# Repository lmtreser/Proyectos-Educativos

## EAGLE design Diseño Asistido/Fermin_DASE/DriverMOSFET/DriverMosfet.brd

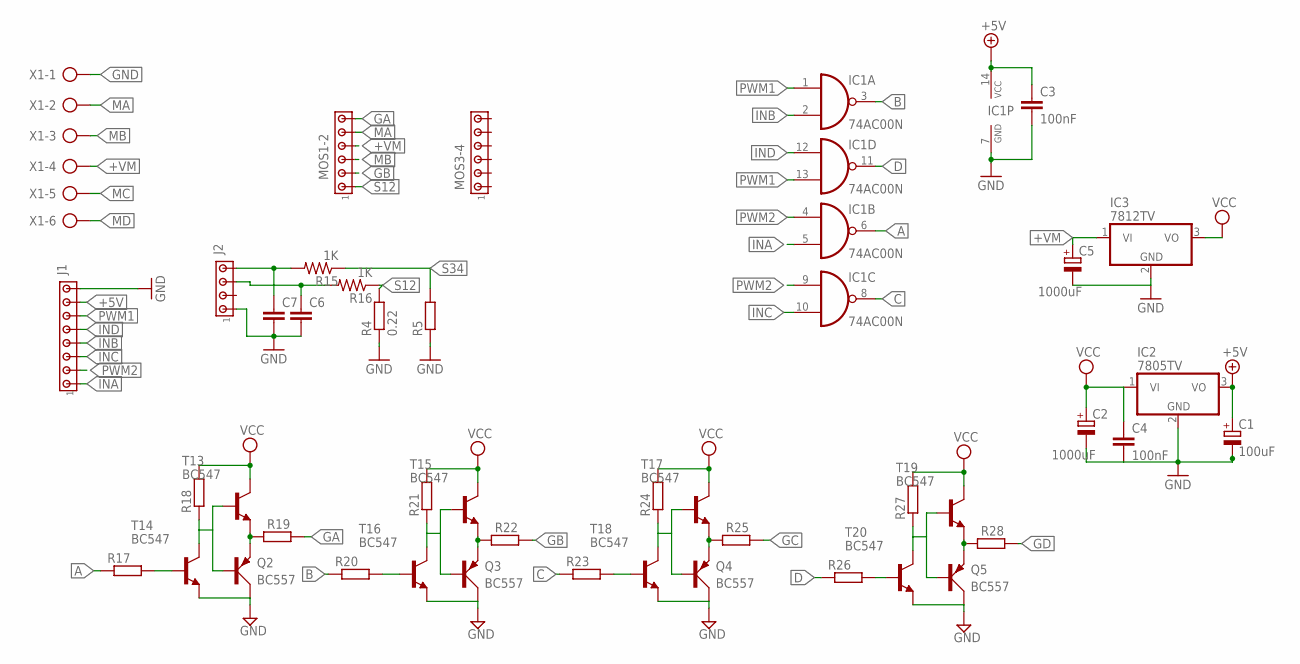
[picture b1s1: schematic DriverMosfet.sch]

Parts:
C1: 100uF; E2,5-6
C2: 1000uF; E3,5-8
C3, C4: 100nF; C050-025X075
C5: 1000uF; E3,5-10
C6, C7: C-EU025-025X050; C025-025X050
IC1: 74AC00N; DIL14
IC2: 7805TV; TO220V
IC3: 7812TV; TO220V
J1: MTA08-100; 10X08MTA
J2: MTA04-100; 10X04MTA
MOS1-2, MOS3-4: MTA06-100; 10X06MTA
Q2, Q3, Q4, Q5: BC557; SOT54A
R4: 0.22; 0411/12
R5: R-EU_0411/12; 0411/12
R15, R16: 1K; 0207/7@1
R17, R18, R19, R20, R21, R22, R23, R24, R25, R26, R27, R28: R-EU_0207/7; 0207/7
T13, T14, T15, T16, T17, T18, T19, T20: BC547; TO92
X1: AK500/6-H

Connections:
+5V: C1.+, C3.1, IC1.14 (VCC), IC2.3 (VO), J1.7
+VM: C5.+, IC3.1 (VI), MOS1-2.4, X1.4
A: IC1.6 (O), R17.1
B: IC1.3 (O), R20.1
C: IC1.8 (O), R23.1
D: IC1.11 (O), R26.1
GA: MOS1-2.6, R19.2
GB: MOS1-2.2, R22.2
GC: R25.2
GD: R28.2
GND: C1.-, C2.-, C3.2, C4.2, C5.-, C6.2, IC1.7 (GND), IC2.2 (GND), IC3.2 (GND), J1.8, J2.1, Q2.C, Q3.C, Q4.C, Q5.C, R4.1, R5.1, T14.1 (E), T16.1 (E), T18.1 (E), T20.1 (E), X1.1
INA: IC1.5 (I1), J1.1
INB: IC1.2 (I1), J1.4
INC: IC1.10 (I1), J1.3
IND: IC1.12 (I0), J1.5
MA: MOS1-2.5, X1.2
MB: MOS1-2.3, X1.3
MC: X1.5
MD: X1.6
unnamed: C7.1, J2.4, R15.2
unnamed: R17.2, T14.2 (B)
unnamed: C6.1, J2.3, R16.2
unnamed: Q3.E, R22.1, T15.1 (E)
unnamed: Q2.E, R19.1, T13.1 (E)
unnamed: Q4.E, R25.1, T17.1 (E)
unnamed: Q2.B, R18.1, T13.2 (B), T14.3 (C)
unnamed: R23.2, T18.2 (B)
unnamed: Q4.B, R24.1, T17.2 (B), T18.3 (C)
unnamed: R20.2, T16.2 (B)
unnamed: Q3.B, R21.1, T15.2 (B), T16.3 (C)
unnamed: Q5.E, R28.1, T19.1 (E)
unnamed: R26.2, T20.2 (B)
unnamed: Q5.B, R27.1, T19.2 (B), T20.3 (C)
PWM1: IC1.1 (I0), IC1.13 (I1), J1.6
PWM2: IC1.4 (I0), IC1.9 (I0), J1.2
S12: MOS1-2.1, R4.2, R16.1
S34: R5.2, R15.1
VCC: C2.+, C4.1, IC2.1 (VI), IC3.3 (VO), R18.2, R21.2, R24.2, R27.2, T13.3 (C), T15.3 (C), T17.3 (C), T19.3 (C)

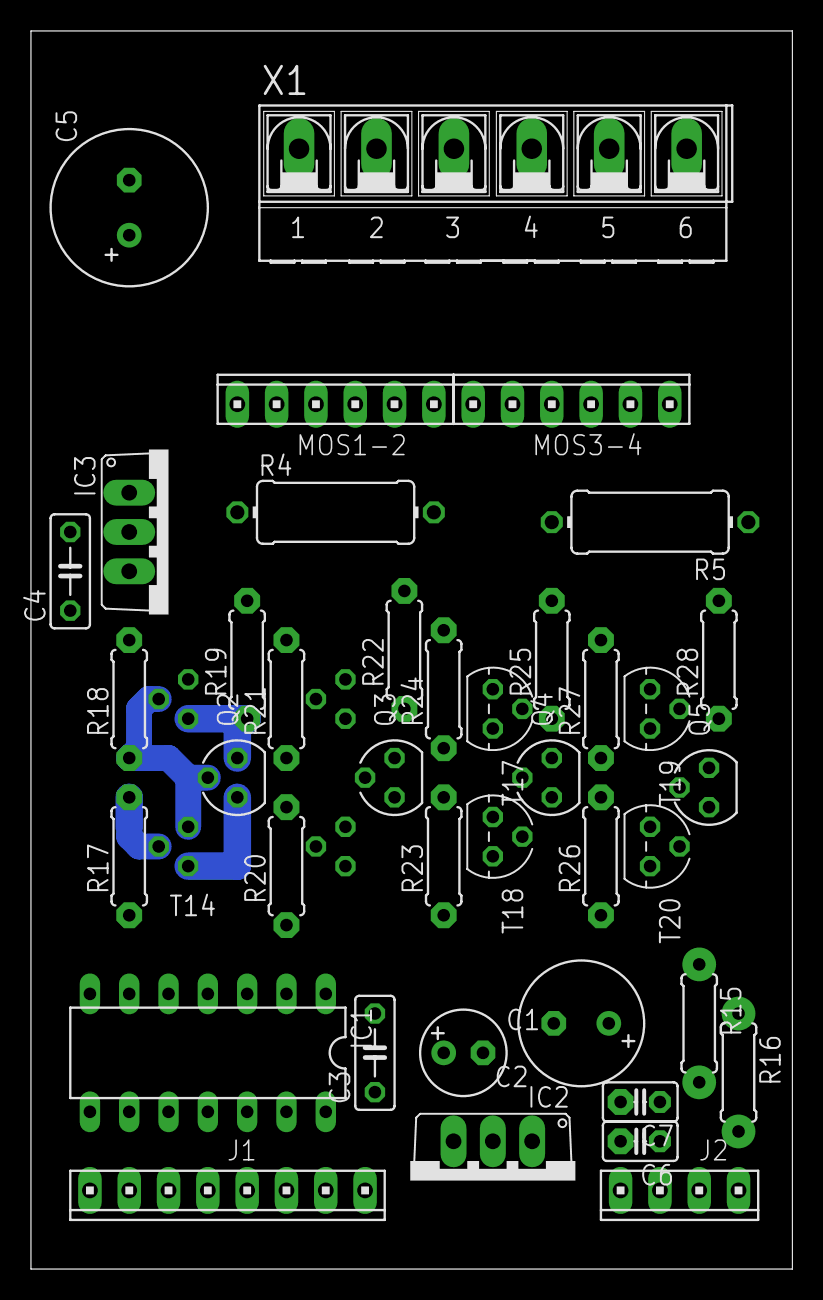
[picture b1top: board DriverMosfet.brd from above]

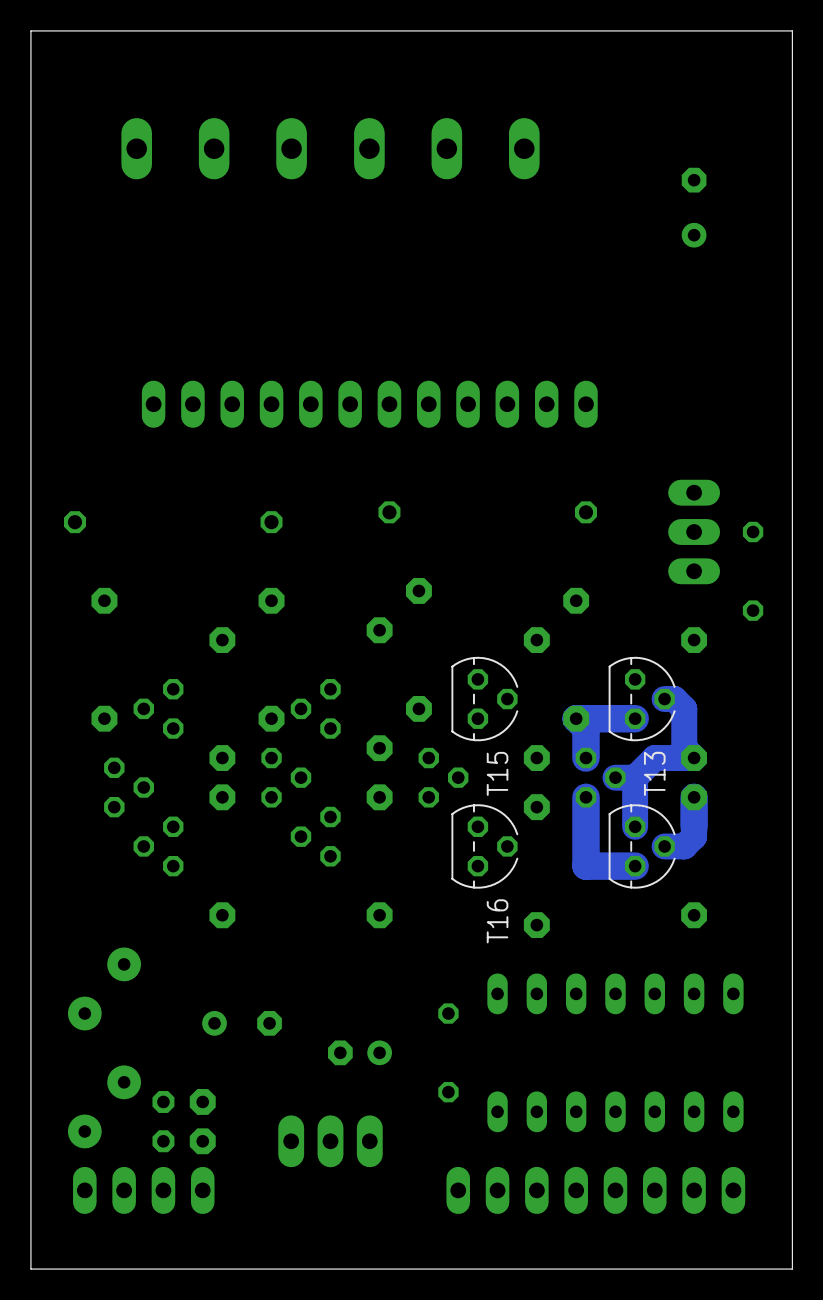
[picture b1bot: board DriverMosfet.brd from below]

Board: 2 copper layers, 49.2 x 80.0 mm, 43 parts (4 on the bottom side), 34 nets.

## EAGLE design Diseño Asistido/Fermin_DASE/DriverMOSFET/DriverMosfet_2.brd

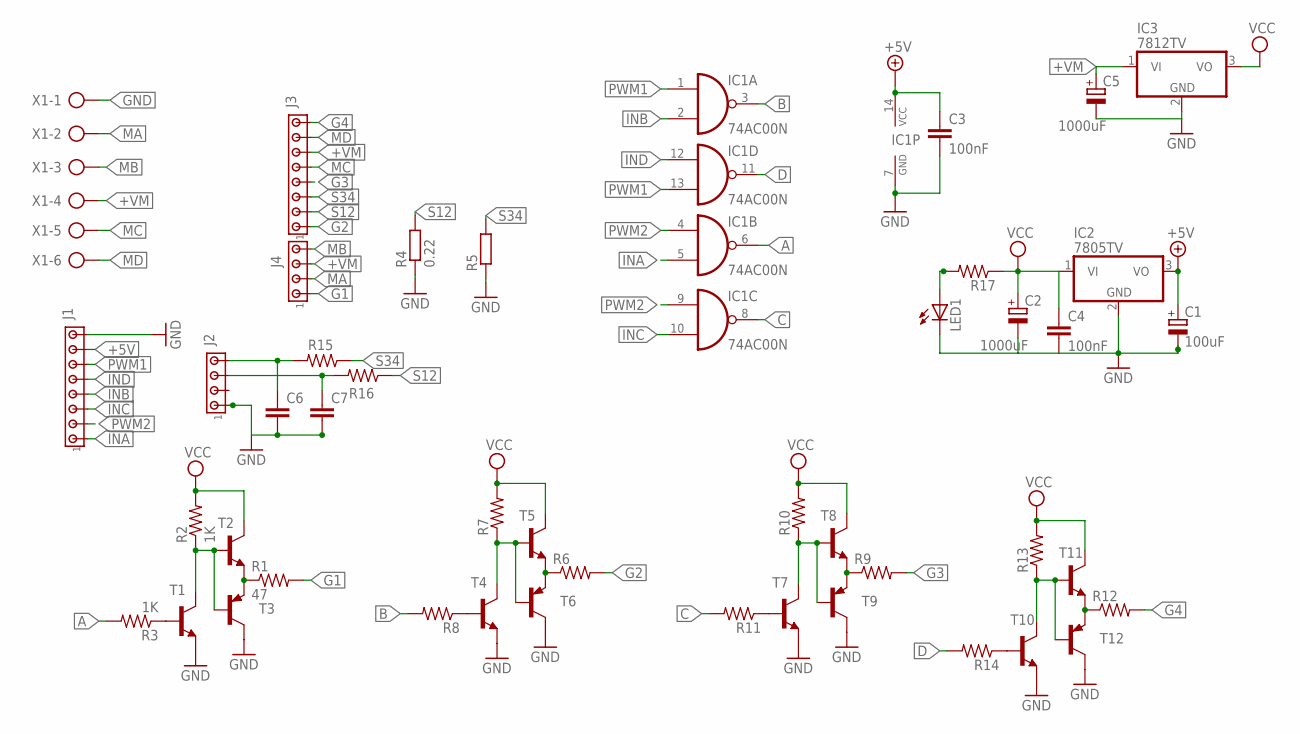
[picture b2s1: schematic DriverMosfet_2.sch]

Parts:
C1: 100uF; E2,5-6
C2: 1000uF; E2,5-7
C3, C4: 100nF; C050-025X075
C5: 1000uF; E3,5-10
C6, C7: C-EU025-030X050; C025-030X050
IC1: 74AC00N; DIL14
IC2: 7805TV; TO220V
IC3: 7812TV; TO220V
J1, J3: MTA08-100; 10X08MTA
J2, J4: MTA04-100; 10X04MTA
LED1: LED3MM
R1: 47; 0207/7
R2, R3: 1K; 0207/7
R4: 0.22; P0613/15
R5: R-EU_0414/15; 0414/15
R6, R7, R8, R9, R10, R11, R12, R13, R14, R15, R16, R17: R-US_0207/7; 0207/7
T1, T2, T4, T5, T7, T8, T10, T11: BC547-NPN-TO92-CBE; TO92-CBE
T3, T6, T9, T12: BC557A-PNP-TO92-EBC; TO92-EBC
X1: AK500/6-H

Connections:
+5V: C1.+, C3.1, IC1.14 (VCC), IC2.3 (VO), J1.7
+VM: C5.+, IC3.1 (VI), J3.6, J4.3, X1.4
A: IC1.6 (O), R3.2
B: IC1.3 (O), R8.2
C: IC1.8 (O), R11.2
D: IC1.11 (O), R14.2
G1: J4.1, R1.2
G2: J3.1, R6.2
G3: J3.4, R9.2
G4: J3.8, R12.2
GND: C1.-, C2.-, C3.2, C4.2, C5.-, C6.2, C7.2, IC1.7 (GND), IC2.2 (GND), IC3.2 (GND), J1.8, J2.1, LED1.K (C), R4.1, R5.1, T1.E, T3.C, T4.E, T6.C, T7.E, T9.C, T10.E, T12.C, X1.1
INA: IC1.5 (I1), J1.1
INB: IC1.2 (I1), J1.4
INC: IC1.10 (I1), J1.3
IND: IC1.12 (I0), J1.5
MA: J4.2, X1.2
MB: J4.4, X1.3
MC: J3.5, X1.5
MD: J3.7, X1.6
unnamed: R1.1, T2.E, T3.E
unnamed: R3.1, T1.B
unnamed: C6.1, J2.4, R15.2
unnamed: R2.1, T1.C, T2.B, T3.B
unnamed: C7.1, J2.3, R16.2
unnamed: R6.1, T5.E, T6.E
unnamed: R8.1, T4.B
unnamed: LED1.A, R17.2
unnamed: R7.1, T4.C, T5.B, T6.B
unnamed: R9.1, T8.E, T9.E
unnamed: R11.1, T7.B
unnamed: R10.1, T7.C, T8.B, T9.B
unnamed: R12.1, T11.E, T12.E
unnamed: R14.1, T10.B
unnamed: R13.1, T10.C, T11.B, T12.B
PWM1: IC1.1 (I0), IC1.13 (I1), J1.6
PWM2: IC1.4 (I0), IC1.9 (I0), J1.2
S12: J3.2, R4.2, R16.1
S34: J3.3, R5.2, R15.1
VCC: C2.+, C4.1, IC2.1 (VI), IC3.3 (VO), R2.2, R7.2, R10.2, R13.2, R17.1, T2.C, T5.C, T8.C, T11.C

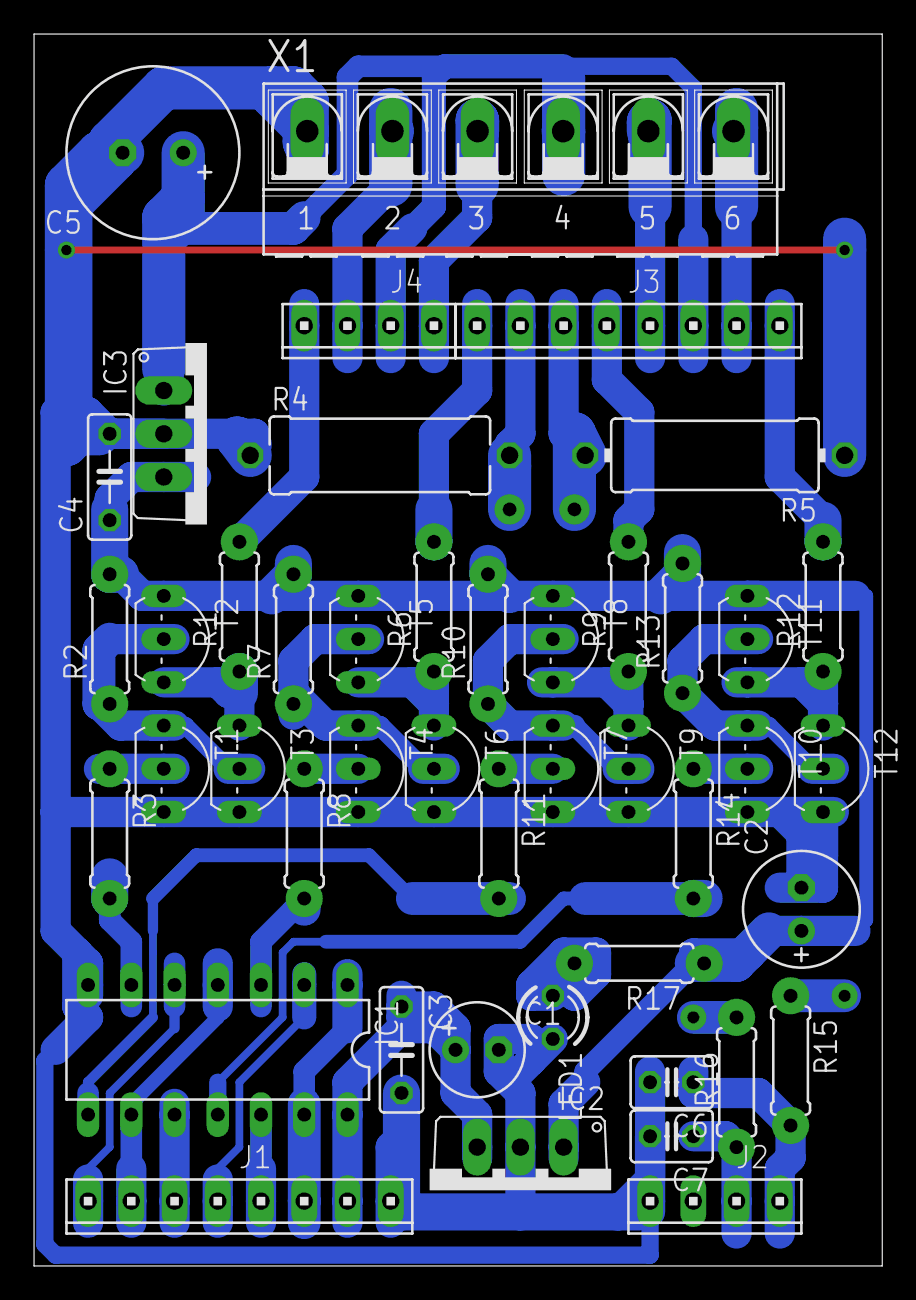
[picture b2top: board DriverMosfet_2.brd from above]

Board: 2 copper layers, 49.8 x 72.4 mm, 45 parts (0 on the bottom side), 39 nets.

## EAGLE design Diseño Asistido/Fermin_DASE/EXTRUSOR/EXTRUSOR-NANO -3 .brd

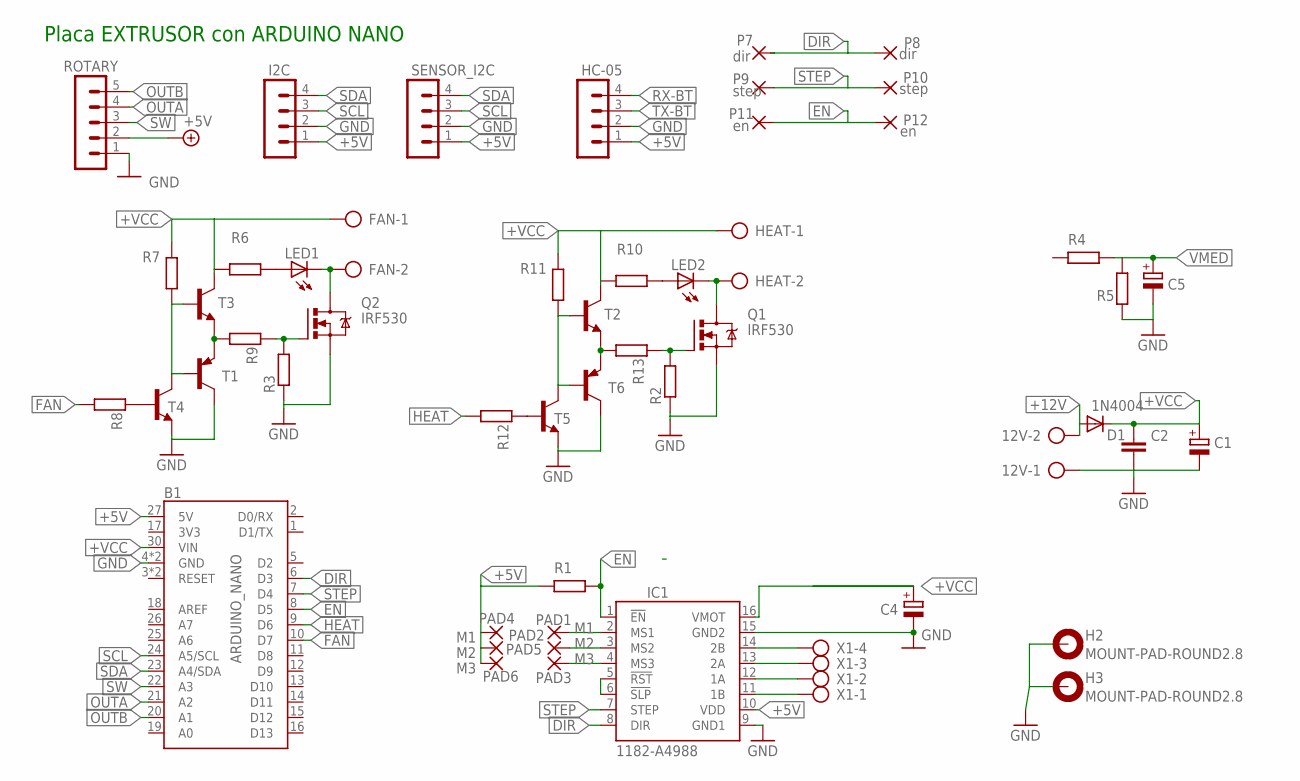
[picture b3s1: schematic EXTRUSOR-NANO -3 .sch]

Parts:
12V: AK500/2
B1: ARDUINO_NANO; NANO
C1: CPOL-EUE2.5-6; E2,5-6
C2: C-EU025-025X050; C025-025X050
C4, C5: CPOL-EUE2.5-5; E2,5-5
D1: 1N4004; DO41-10
FAN: AK500/2
H2, H3: MOUNT-PAD-ROUND2.8; 2,8-PAD
HC-05: MA04-1
HEAT: AK500/2
I2C: MA04-1
IC1: 1182-A4988; A4988
LED1, LED2: LED3MM; LED_3MM
P7, P8: dir; 1,6/0,9
P9, P10: step; 1,6/0,9
P11, P12: en; 1,6/0,9
PAD1, PAD4: M1; 1,6/0,9
PAD2, PAD5: M2; 1,6/0,9
PAD3, PAD6: M3; 1,6/0,9
Q1, Q2: IRF530; TO220BV
R1, R2, R3, R4, R5, R6, R7, R8, R9, R10, R11, R12, R13: R-EU_0207/7; 0207/7
ROTARY: MA05-1
SENSOR_I2C: MA04-1
T1, T6: 2N4126-PNP-TO92-CBE; TO92-CBE
T2, T3, T4, T5: -NPN-TO92-EBC; TO92-EBC
X1: AK500/4

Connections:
+5V: B1.27 (5V), HC-05.1, I2C.1, IC1.10 (VDD), PAD4.1, PAD5.1, PAD6.1, R1.1, ROTARY.2, SENSOR_I2C.1
+12V: 12V.2, D1.A
+VCC: B1.30 (VIN), C1.+, C2.1, C4.+, D1.C, FAN.1, HEAT.1, IC1.16 (VMOT), R6.2, R7.2, R10.2, R11.2, T2.C, T3.C
DIR: B1.6 (D3), IC1.8 (DIR), P7.1, P8.1
EN: B1.8 (D5), IC1.1 (!EN), P11.1, P12.1, R1.2
FAN: B1.10 (D7), R8.2
GND: 12V.1, B1.4 (GND), B1.29 (GND), C1.-, C2.2, C4.-, C5.-, H2.B2,8, H3.B2,8, HC-05.2, I2C.2, IC1.9 (GND1), IC1.15 (GND2), Q1.S, Q2.S, R2.1, R3.1, R5.1, ROTARY.1, SENSOR_I2C.2, T1.C, T4.E, T5.E, T6.C
HEAT: B1.9 (D6), R12.2
unnamed: IC1.5 (!RST), IC1.6 (!SLP)
unnamed: IC1.4 (MS3), PAD3.1
unnamed: IC1.3 (MS2), PAD2.1
unnamed: IC1.14 (2B), X1.4
unnamed: IC1.2 (MS1), PAD1.1
unnamed: LED1.A, R6.1
unnamed: Q2.G, R3.2, R9.1
unnamed: R9.2, T1.E, T3.E
unnamed: IC1.13 (2A), X1.3
unnamed: IC1.12 (1A), X1.2
unnamed: IC1.11 (1B), X1.1
unnamed: LED2.A, R10.1
unnamed: FAN.2, LED1.K (C), Q2.D
unnamed: R7.1, T1.B, T3.B, T4.C
unnamed: R8.1, T4.B
unnamed: Q1.G, R2.2, R13.1
unnamed: HEAT.2, LED2.K (C), Q1.D
unnamed: R13.2, T2.E, T6.E
unnamed: R11.1, T2.B, T5.C, T6.B
unnamed: R12.1, T5.B
OUTA: B1.21 (A2), ROTARY.4
OUTB: B1.20 (A1), ROTARY.5
RX-BT: HC-05.4
SCL: B1.24 (A5/SCL), I2C.3, SENSOR_I2C.3
SDA: B1.23 (A4/SDA), I2C.4, SENSOR_I2C.4
STEP: B1.7 (D4), IC1.7 (STEP), P9.1, P10.1
SW: B1.22 (A3), ROTARY.3
TX-BT: HC-05.3
VMED: C5.+, R4.2, R5.2

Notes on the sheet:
Placa EXTRUSOR con ARDUINO NANO

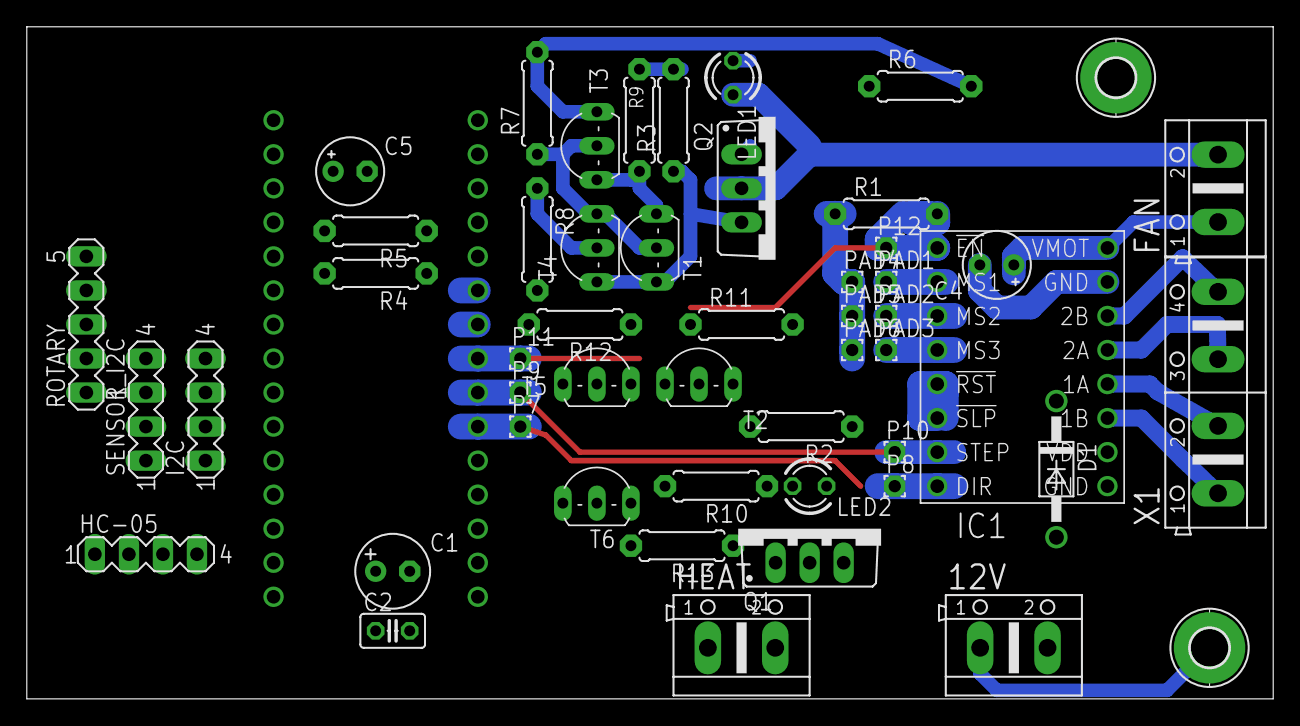
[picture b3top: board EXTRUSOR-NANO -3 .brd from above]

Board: 2 copper layers, 93.0 x 50.2 mm, 52 parts (0 on the bottom side), 35 nets.

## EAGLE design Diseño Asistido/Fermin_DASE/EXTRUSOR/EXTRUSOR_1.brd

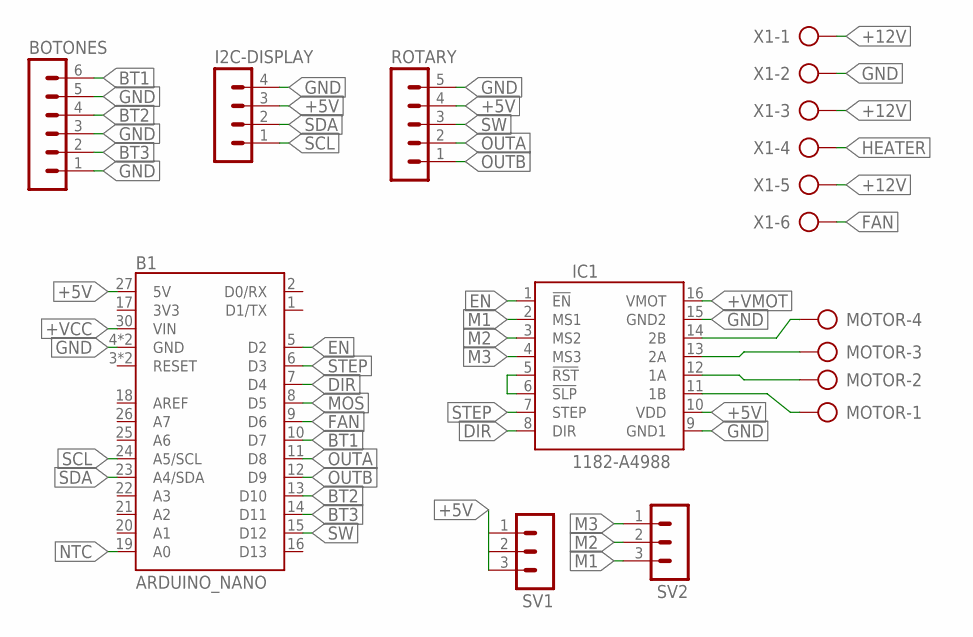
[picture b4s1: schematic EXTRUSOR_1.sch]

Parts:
B1: ARDUINO_NANO; NANO
BOTONES: MA06-1
I2C-DISPLAY: MA04-1
IC1: 1182-A4988; A4988
MOTOR: AK500/4
ROTARY: MA05-1
SV1, SV2: MA03-1
X1: AK500/6

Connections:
+5V: B1.27 (5V), I2C-DISPLAY.3, IC1.10 (VDD), IC1.11 (1B), MOTOR.1, ROTARY.4, SV1.1, SV1.2, SV1.3
+12V: X1.1, X1.3, X1.5
+VCC: B1.30 (VIN)
+VMOT: IC1.16 (VMOT)
BT1: BOTONES.6
BT2: BOTONES.4
BT3: BOTONES.2
DIR: IC1.8 (DIR)
EN: B1.5 (D2), IC1.1 (!EN)
FAN: X1.6
GND: B1.4 (GND), B1.29 (GND), BOTONES.1, BOTONES.3, BOTONES.5, I2C-DISPLAY.4, IC1.9 (GND1), IC1.15 (GND2), ROTARY.5, X1.2
HEATER: X1.4
M1: IC1.2 (MS1), SV2.3
M2: IC1.3 (MS2), SV2.2
M3: IC1.4 (MS3), SV2.1
unnamed: IC1.12 (1A), MOTOR.2
unnamed: IC1.13 (2A), MOTOR.3
unnamed: IC1.14 (2B), MOTOR.4
unnamed: IC1.5 (!RST), IC1.6 (!SLP)
NTC: B1.19 (A0)
OUTA: ROTARY.2
OUTB: ROTARY.1
SCL: B1.24 (A5/SCL), I2C-DISPLAY.1
SDA: B1.23 (A4/SDA), I2C-DISPLAY.2
STEP: IC1.7 (STEP)
SW: ROTARY.3

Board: 2 copper layers, 9 parts (0 on the bottom side), 13 nets, no tracks yet.

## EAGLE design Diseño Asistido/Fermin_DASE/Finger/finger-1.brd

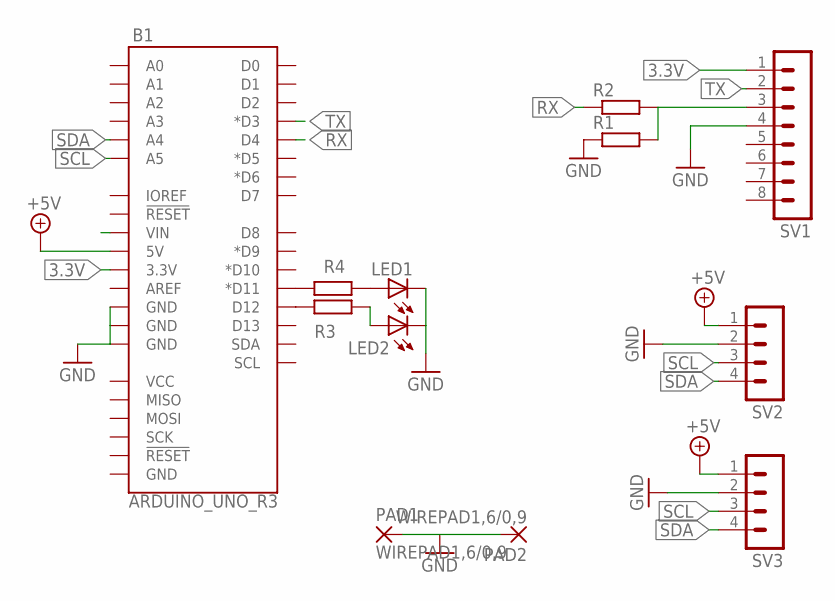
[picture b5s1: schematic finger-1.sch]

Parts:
B1: ARDUINO_UNO_R3; ARDUINO_R3
LED1, LED2: LED3MM
PAD1, PAD2: WIREPAD1,6/0,9; 1,6/0,9
R1, R2, R3, R4: R-EU_0207/7; 0207/7
SV1: MA08-1
SV2, SV3: MA04-1

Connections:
3.3V: B1.3.3V, SV1.1
+5V: B1.5V, SV2.1, SV3.1
GND: B1.GND@2 (GND), B1.GND@3 (GND), B1.GND@4 (GND), LED1.K (C), LED2.K (C), PAD1.1, PAD2.1, R1.1, SV1.4, SV2.2, SV3.2
unnamed: B1.D12, R3.1
unnamed: B1.D11 (*D11), R4.1
unnamed: LED2.A, R3.2
unnamed: LED1.A, R4.2
unnamed: R1.2, R2.2, SV1.3
RX: B1.D4, R2.1
SCL: B1.A5, SV2.3, SV3.3
SDA: B1.A4, SV2.4, SV3.4
TX: B1.D3 (*D3), SV1.2

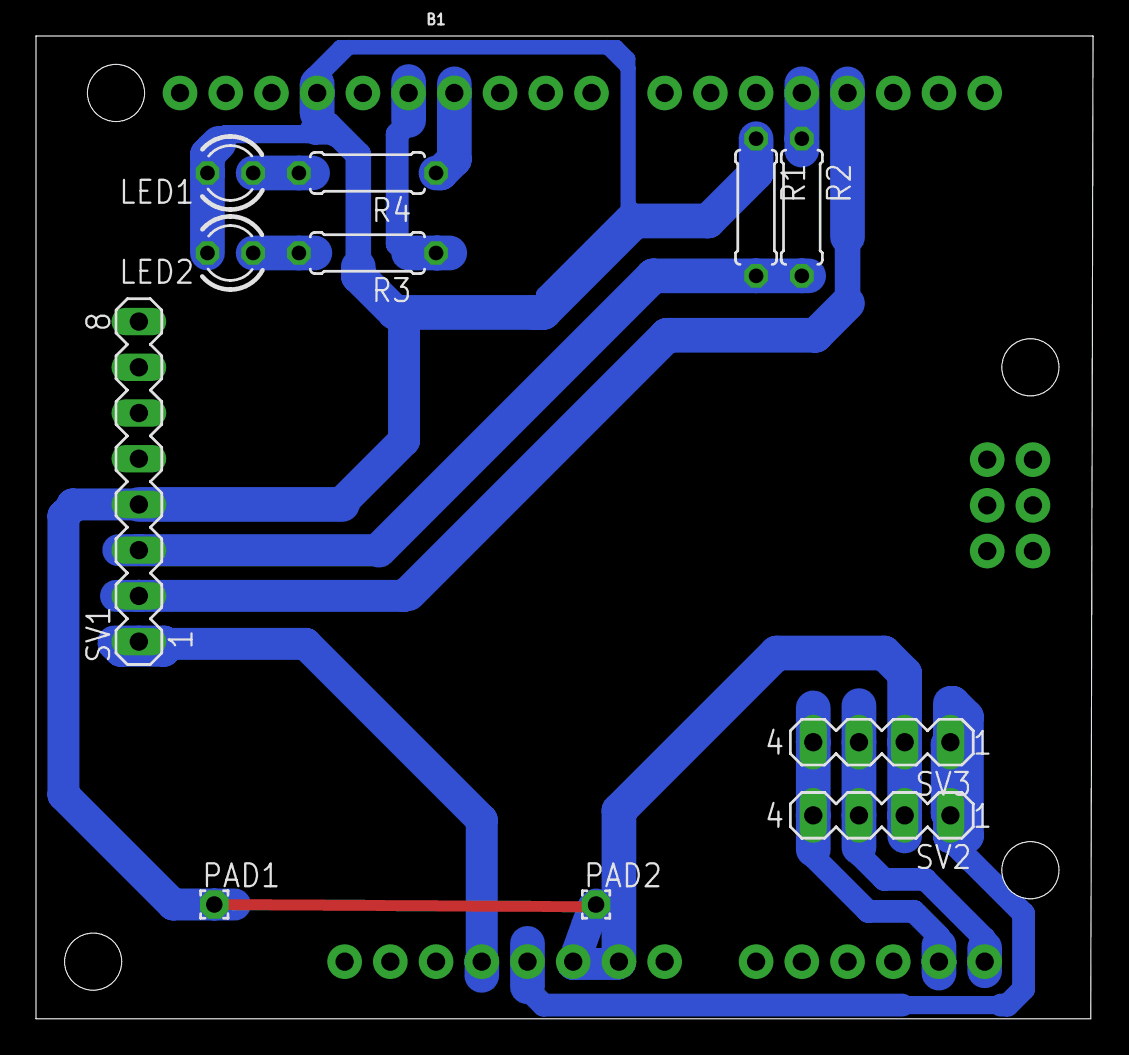
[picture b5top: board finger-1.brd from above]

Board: 2 copper layers, 58.7 x 54.6 mm, 12 parts (0 on the bottom side), 12 nets.

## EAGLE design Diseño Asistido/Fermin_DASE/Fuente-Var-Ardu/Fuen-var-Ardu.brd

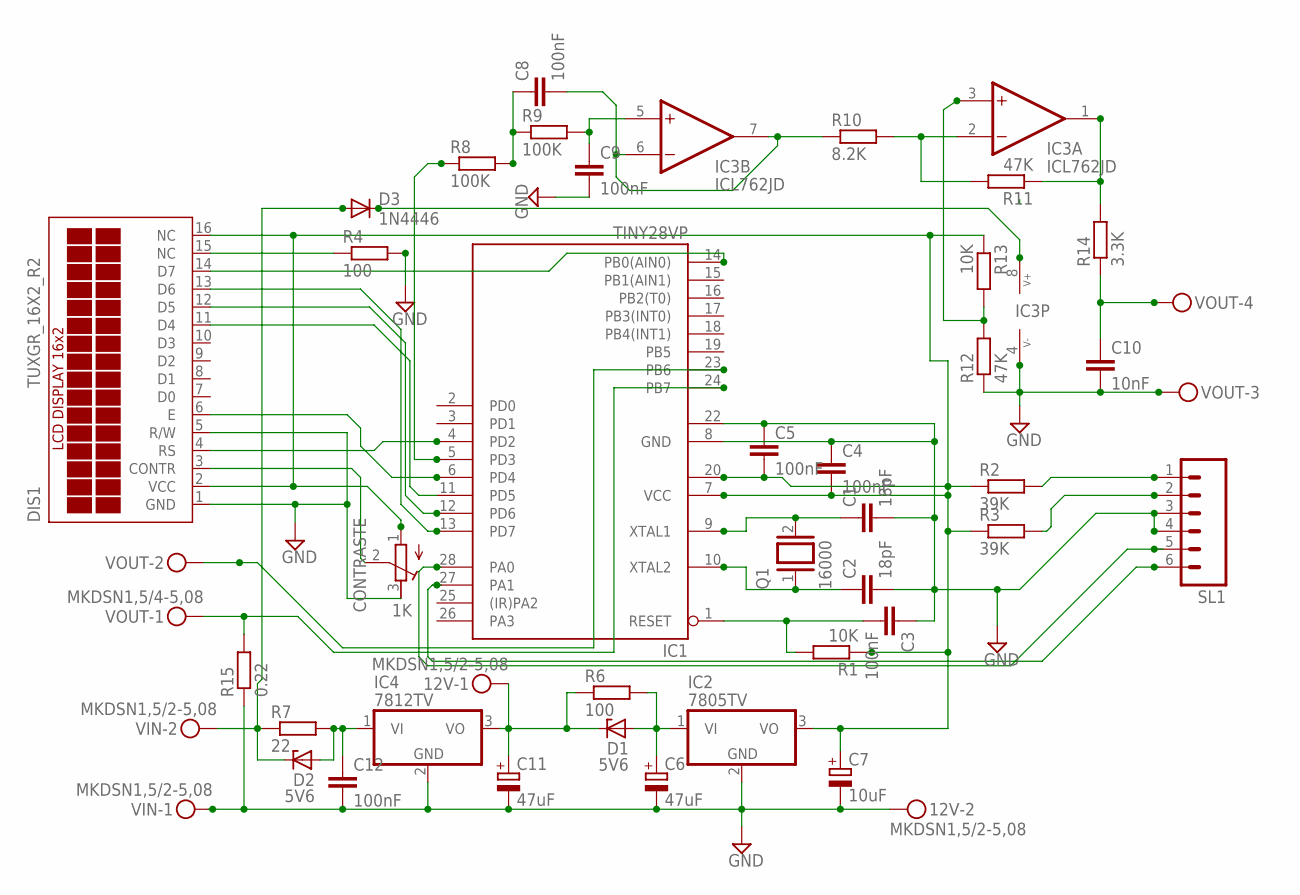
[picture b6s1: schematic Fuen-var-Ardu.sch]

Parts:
12V: MKDSN1,5/2-5,08
C1, C2: 18pF; C025-025X050
C3, C5, C8, C9, C12: 100nF; C050-025X075
C4: 100nF; C075-032X103
C6, C11: 47uF; E2,5-7
C7: 10uF; E2,5-7
C10: 10nF; C050-025X075
CONTRASTE: 1K; RTRIM3296W
D1, D2: 5V6; DO35Z10
D3: 1N4446; DO35-10
DIS1: TUXGR_16X2_R2
IC1: TINY28VP; DIL28-3
IC2: 7805TV; TO220V
IC3: ICL762JD; DIL08
IC4: 7812TV; TO220V
Q1: 16000; Q
R1, R13: 10K; 0207/10
R2, R3: 39K; 0207/10
R4: 100; 0207/15
R6: 100; 0411/12
R7: 22; 0411/12
R8, R9: 100K; 0207/10
R10: 8.2K; 0207/10
R11, R12: 47K; 0207/10
R14: 3.3K; 0207/10
R15: 0.22; P0817/22
SL1: M06; 06P
VIN: MKDSN1,5/2-5,08
VOUT: MKDSN1,5/4-5,08

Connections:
GND: 12V.2, C1.2, C2.2, C3.1, C4.1, C5.1, C6.-, C7.-, C9.2, C10.2, C11.-, C12.2, DIS1.1 (GND), IC1.8 (GND), IC1.22 (GND1), IC2.2 (GND), IC3.4 (V-), IC4.2 (GND), R4.2, R12.1, R15.1, SL1.3, SL1.4, VIN.1, VOUT.3
unnamed: C3.2, IC1.1 (RESET), R1.2
unnamed: C2.1, IC1.10 (XTAL2), Q1.1
unnamed: C1.1, IC1.9 (XTAL1), Q1.2
unnamed: C4.2, C5.2, C7.+, CONTRASTE.1 (A), DIS1.2 (VCC), DIS1.16 (NC), IC1.7 (VCC), IC1.20 (VCC1), IC2.3 (VO), R1.1, R2.1, R3.1, R13.1
unnamed: DIS1.13 (D6), IC1.13 (PD7)
unnamed: IC1.24 (PB7), R15.2, VOUT.1
unnamed: CONTRASTE.2 (S), DIS1.3 (CONTR)
unnamed: DIS1.14 (D7), IC1.14 (PB0(AIN0))
unnamed: CONTRASTE.3 (E), DIS1.5 (R/W)
unnamed: D3.C, IC3.8 (V+)
unnamed: DIS1.12 (D5), IC1.12 (PD6)
unnamed: IC1.23 (PB6), VOUT.2
unnamed: IC1.27 (PA1), SL1.6
unnamed: DIS1.11 (D4), IC1.11 (PD5)
unnamed: C6.+, D1.A, IC2.1 (VI), R6.2
unnamed: R2.2, SL1.1
unnamed: C10.1, R14.1, VOUT.4
unnamed: DIS1.4 (RS), IC1.4 (PD2)
unnamed: IC3.3 (+IN), R12.2, R13.2
unnamed: DIS1.15 (NC), R4.1
unnamed: DIS1.6 (E), IC1.6 (PD4)
unnamed: 12V.1, C11.+, D1.C, IC4.3 (VO), R6.1
unnamed: R3.2, SL1.2
unnamed: IC3.1 (OUT), R11.1, R14.2
unnamed: C8.2, IC3.6 (-IN), IC3.7 (OUT), R10.1
unnamed: IC3.2 (-IN), R10.2, R11.2
unnamed: C8.1, R8.2, R9.1
unnamed: C9.1, IC3.5 (+IN), R9.2
unnamed: C12.1, D2.A, IC4.1 (VI), R7.2
unnamed: IC1.5 (PD3), R8.1
unnamed: IC1.28 (PA0), SL1.5
unnamed: D2.C, D3.A, R7.1, VIN.2

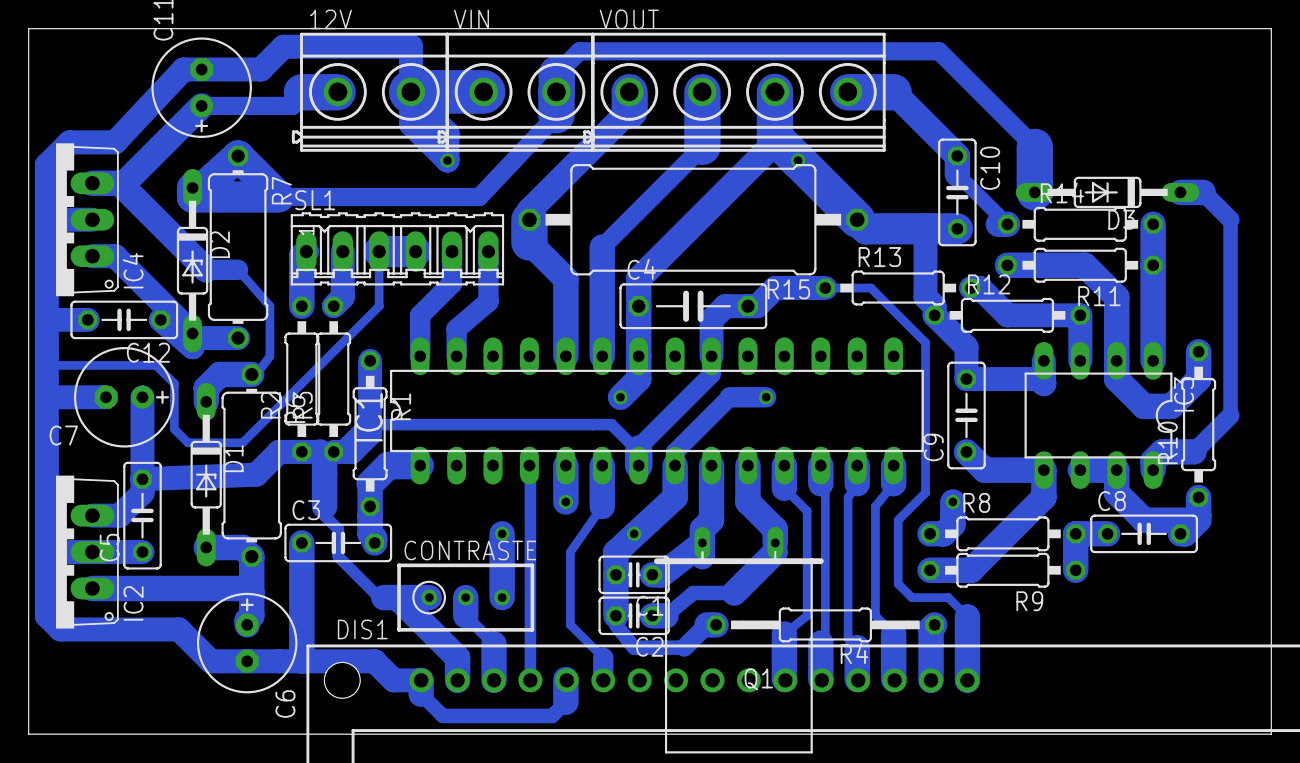
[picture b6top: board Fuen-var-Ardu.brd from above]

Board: 2 copper layers, 86.7 x 49.2 mm, 40 parts (0 on the bottom side), 33 nets.

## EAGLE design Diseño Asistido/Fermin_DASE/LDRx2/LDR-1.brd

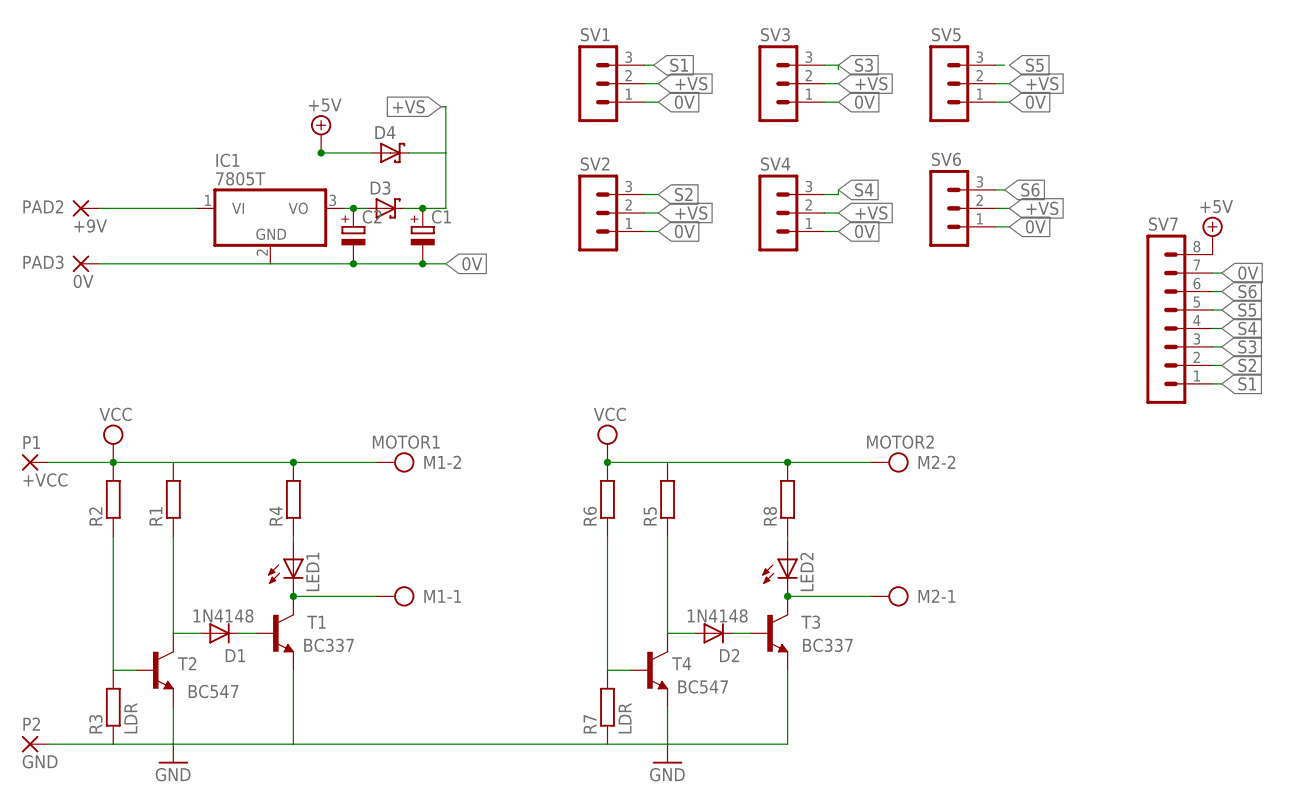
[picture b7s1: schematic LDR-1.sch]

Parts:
C1, C2: CPOL-EUE2.5-5; E2,5-5
D1, D2: 1N4148; DO35-7
D3, D4: SCHOTTKY-DIODEDO35-7; DIODE_DO35-7
IC1: 7805T; TO220H
LED1, LED2: LED3MM
M1: MOTOR1; AK500/2
M2: MOTOR2; AK500/2
P1: +VCC; 2,15/1,0
P2: GND; 2,15/1,0
PAD2: +9V; 2,15/1,0
PAD3: 0V; 2,15/1,0
R1, R2, R4, R5, R6, R8: R-EU_0207/7; 0207/7
R3, R7: LDR; 0204/5
SV1, SV2, SV3, SV4, SV5, SV6: MA03-1
SV7: MA08-1
T1, T3: BC337; TO92-CBE
T2, T4: BC547; TO92-CBE

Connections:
0V: C1.-, C2.-, IC1.2 (GND), PAD3.1, SV1.1, SV2.1, SV3.1, SV4.1, SV5.1, SV6.1, SV7.7
+5V: D4.A (C), SV7.8
+VS: C1.+, D3.C (A), D4.C (A), SV1.2, SV2.2, SV3.2, SV4.2, SV5.2, SV6.2
GND: P2.1, R3.1, R7.1, T1.E, T2.E, T3.E, T4.E
unnamed: D1.C, T1.B
unnamed: D1.A, R1.1, T2.C
unnamed: LED1.K (C), M1.1, T1.C
unnamed: C2.+, D3.A (C), IC1.3 (VO)
unnamed: LED1.A, R4.1
unnamed: R2.1, R3.2, T2.B
unnamed: D2.C, T3.B
unnamed: D2.A, R5.1, T4.C
unnamed: LED2.K (C), M2.1, T3.C
unnamed: R6.1, R7.2, T4.B
unnamed: LED2.A, R8.1
unnamed: IC1.1 (VI), PAD2.1
S1: SV1.3, SV7.1
S2: SV2.3, SV7.2
S3: SV3.3, SV7.3
S4: SV4.3, SV7.4
S5: SV5.3, SV7.5
S6: SV6.3, SV7.6
VCC: M1.2, M2.2, P1.1, R1.2, R2.2, R4.2, R5.2, R6.2, R8.2

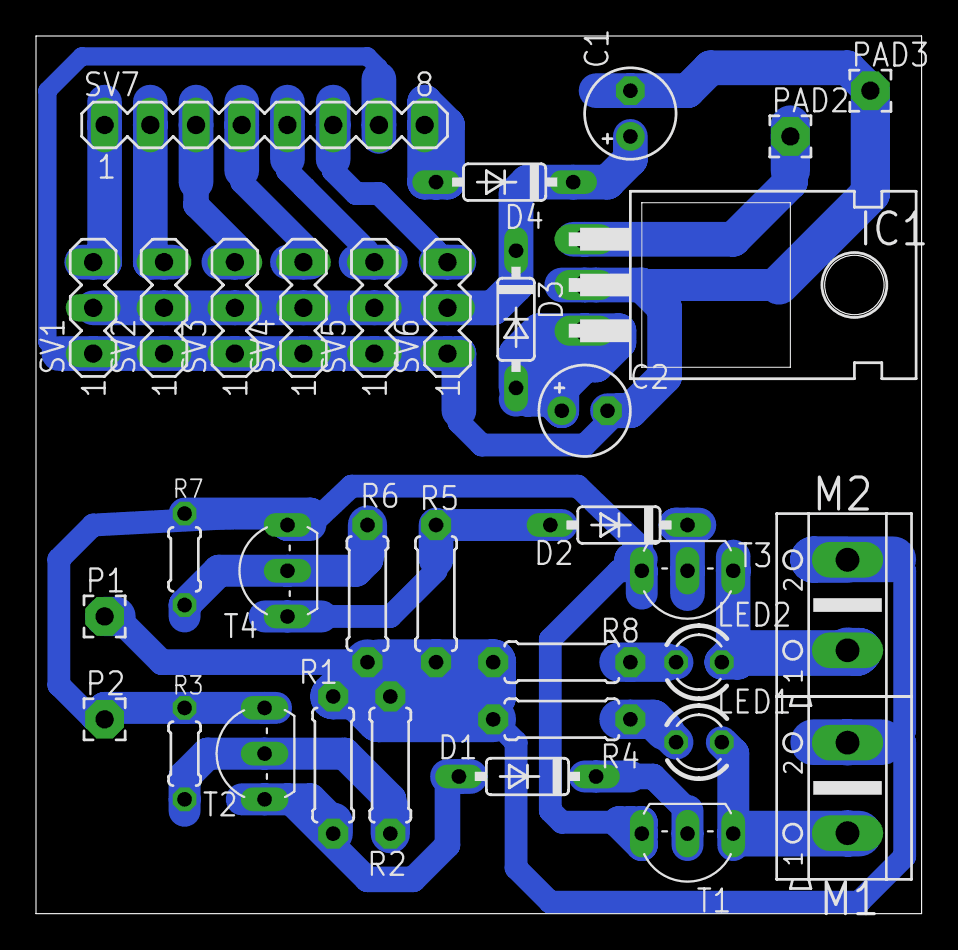
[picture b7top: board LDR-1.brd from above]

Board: 2 copper layers, 49.2 x 48.8 mm, 34 parts (0 on the bottom side), 23 nets.
